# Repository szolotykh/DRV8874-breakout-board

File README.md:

# Motor Controller DRV8874

The Motor Controller, harnessing the power of the DRV8874 H-bridge motor driver by Texas Instruments, offers a top-of-the-line solution for managing small to large DC motors. This compact yet potent device presents an expansive operating supply voltage range of 4.5V to 37V, assuring adaptability with diverse power inputs. It is capable of delivering a peak current of up to a remarkable 6A, ensuring smooth and efficient motor operations even under strenuous conditions. Armed with advanced safety and protection features including overcurrent, thermal, undervoltage, and even charge pump undervoltage, the motor controller prioritizes your motor's durability and reliable performance. Whether your project involves creating a versatile home appliance, an interactive toy robot, or an advanced servo motor system, this motor controller delivers effortless integration and superior performance, empowering your projects with precision and power.

## Features
- PWM control
- PH/EN control
- Motor Voltage 4.5V to 37V
- Peak current 6A
- Current limit 6A
- PWM frequency upto 100 kHz
- 200-mΩ (High-Side + Low-Side)
- Dimensions 27 mm x 40 mm
- Mounting hole diameter 3.2 mm
- Integrated current sensing and regulation
- Undervoltage lockout
- Charge pump undervoltage
- Overcurrent protection
- Thermal shutdown
- Automatic fault recovery
- Fault indicator pin (nFAULT)
Note: For more information refer to DRV8874 datasheet.

## Control Modes

The DRV8874 Breakout Board supports two different control modes: PH/EN and PWM. The PH/EN mode uses the PH and EN pins to control the motor, while the PWM mode uses the IN1 and IN2 pins and PWM signals to control the motor.

To switch between the control modes, you need to change the position of the "PH/EN|PWM" jumper on the board. When the jumper is in the PH/EN position, the board is in PH/EN mode. When the jumper is in the PWM position, the board is in PWM mode.

## Arduino Examples

* [PWM Control](./exampes/PWMControl/PWMControl.ino)
* [PH/EN Control](./exampes/PHENControl/PHENControl.ino)
* [Current Sensing](./exampes/CurrentSensing/CurrentSensing.ino)

## Resources

- [Texas Instruments DRV8874](https://www.ti.com/lit/ds/symlink/drv8874.pdf?ts=1678750825020&ref_url=https%253A%252F%252Fwww.ti.com%252Fproduct%252FDRV8874)

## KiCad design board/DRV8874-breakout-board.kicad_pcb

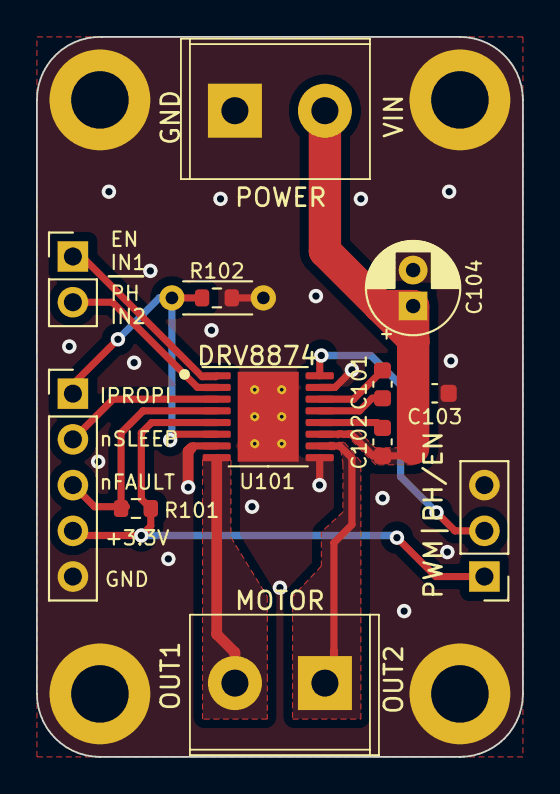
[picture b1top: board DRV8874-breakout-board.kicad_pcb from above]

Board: 2 copper layers, 27.0 x 40.0 mm, 17 parts (0 on the bottom side), 14 nets.

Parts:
C101: 22nf; C_0603_1608Metric
C102, C103: 0.1uf; C_0603_1608Metric
C104: 47u; CP_Radial_D5.0mm_P2.00mm
H101, H102, H103, H104: MountingHole; MountingHole_3.2mm_M3_DIN965_Pad
J101, J103: M0_CONN; JILN JL126-50002G01
J102: Conn_01x02_Pin; PinHeader_1x02_P2.54mm_Vertical
J104: Conn_01x06_Pin; PinHeader_1x05_P2.54mm_Vertical
J105: PMODE; PinHeader_1x03_P2.54mm_Vertical
R101: 10K; R_0603_1608Metric
R102: 1.2K; R_0603_1608Metric
R103: R_Axial_DIN0204_L3.6mm_D1.6mm_P5.08mm_Horizontal
U101: HTSSOP-16-1EP_4.4x5mm_P0.65mm_EP3.4x5mm_Mask2.46x2.31mm_The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

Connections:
+3V3: J104.4, J105.1, R101.1, U101.5 (VREF)
GND: C103.1, C104.2, H101.1, H102.1, H103.1, H104.1, J103.1, J104.5, J105.3, R102.2, R103.2, U101.7 (IMODE), U101.9 (PGND), U101.15 (GND), U101.17 (Pad)
IN1: J102.1, U101.1 (EN/IN1)
IN2: J102.2, U101.2 (PH/IN2)
IPROPI: J104.1, R102.1, R103.1, U101.6 (IPROPI)
unnamed: C101.1, U101.13 (CPH)
unnamed: C101.2, U101.14 (CPL)
unnamed: C102.2, U101.12 (VCP)
OUT1: J101.2, U101.8 (OUT1)
OUT2: J101.1, U101.10 (OUT2)
PMODE: J105.2, U101.16 (PMODE)
VMOTORS: C102.1, C103.2, C104.1, J103.2, U101.11 (VM)
nFAULT: J104.3, R101.2, U101.4 (nFAULT)
nSLEEP: J104.2, U101.3 (nSLEEP)

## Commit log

2023-03-17 Initial version
2023-03-19 Additional changes
2023-03-22 First release version
2023-04-11 Added external resistor
2023-04-12 Fixed issue with text
2023-04-21 Added trace zones
2023-04-21 Update screw terminal
2023-06-18 Create LICENSE
2023-07-12 Update board files
2023-07-12 Update arduino examples
